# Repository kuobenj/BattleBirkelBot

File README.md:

# BirkelBot Battlebot Repo
This repository is for the code and other files related to Team Unobtanium's Battlebot for the Combotics competition held annually at the University of Illinois at Urbana Champaign.

Team Unobtanium is:
* Matt Birkel - Team Captain, Mechanical Design, Software
* Benjamin Kuo - Electrical Design, Software

### Folder Structure
* Robot - This is robot side code. For now this should largely be arduino code for the arduino on board the robot.
* DriverStation - This is the operator side code. This is the code that runs on a driverstation computer.
* Arduino_Calibration_Stuff - This is a folder for a tool to use the arduino to calibrate ESC's
* PCB_files is a directory that holds the EAGLE files for the custom "motherboard" for the robot. This directory also features a reworked design of a PCB for hall effect sensors to sensor 35mm outrunner brushless motors.

### Dependencies
The Robot code is written for an Arduino Pro Mini. As such the Arduino IDE is required to compile and upload the Arduino-side code. The Arduino IDE offers a variety of Libraries for use. This project utilizes

* Encoder by Paul Stoffregen (version 1.4.1)
* PID by Brett Beauregard (version 1.2.0)

To install these libraries

- Go to 'Sketch' -> 'Include Library' -> 'Manage Libraries...'
- Search '<package-name>'
- Install '<package-name>'

The DriverStation code is a pythons script. Below are a potentially non-exhaustive list of the required dependencies.

* pygame - For grabbing joystick values
* serial - For writing to the serial out for the Xbee communication

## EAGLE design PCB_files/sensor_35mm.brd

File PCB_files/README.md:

The sensor_35mm files are all inspired by Equals Zero Designs

"Mount CAD" directory is for the mount to the motor for the sensors

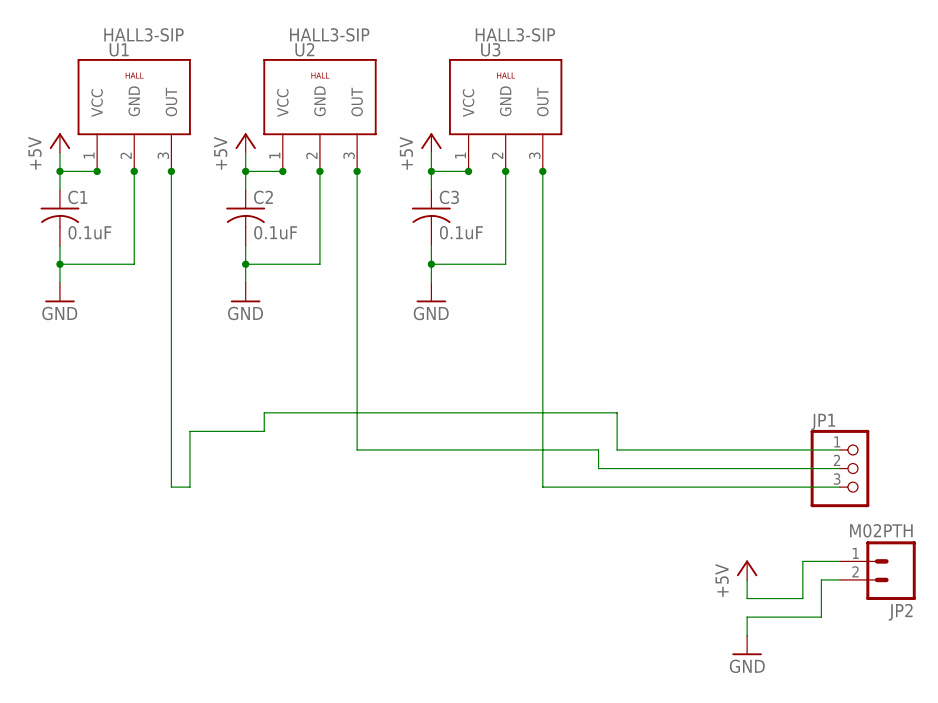
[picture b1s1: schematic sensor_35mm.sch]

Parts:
C1, C2, C3: 0.1uF; C0603
JP1: PINHD-1X3CB; 1X03-CLEANBIG
JP2: M02PTH; 1X02
U1, U2, U3: HALL3-SIP; 3PINS1,27

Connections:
+5V: C1.1, C2.1, C3.1, JP2.1, U1.1 (VCC), U2.1 (VCC), U3.1 (VCC)
GND: C1.2, C2.2, C3.2, JP2.2, U1.2 (GND), U2.2 (GND), U3.2 (GND)
unnamed: JP1.1, U1.3 (OUT)
unnamed: JP1.3, U3.3 (OUT)
unnamed: JP1.2, U2.3 (OUT)

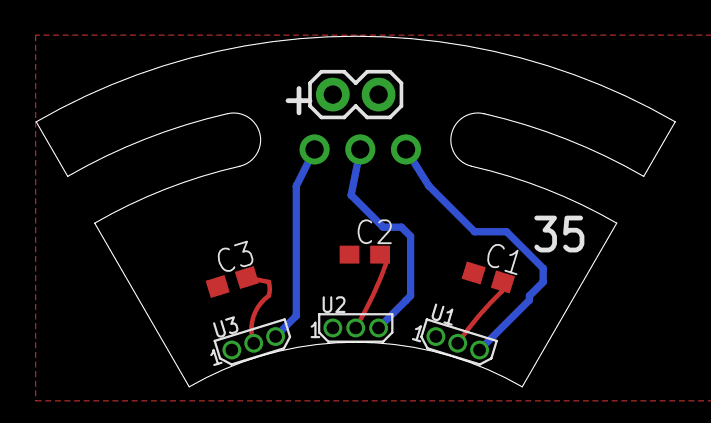
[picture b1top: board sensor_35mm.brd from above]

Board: 2 copper layers, 35.5 x 19.5 mm, 8 parts (0 on the bottom side), 5 nets.

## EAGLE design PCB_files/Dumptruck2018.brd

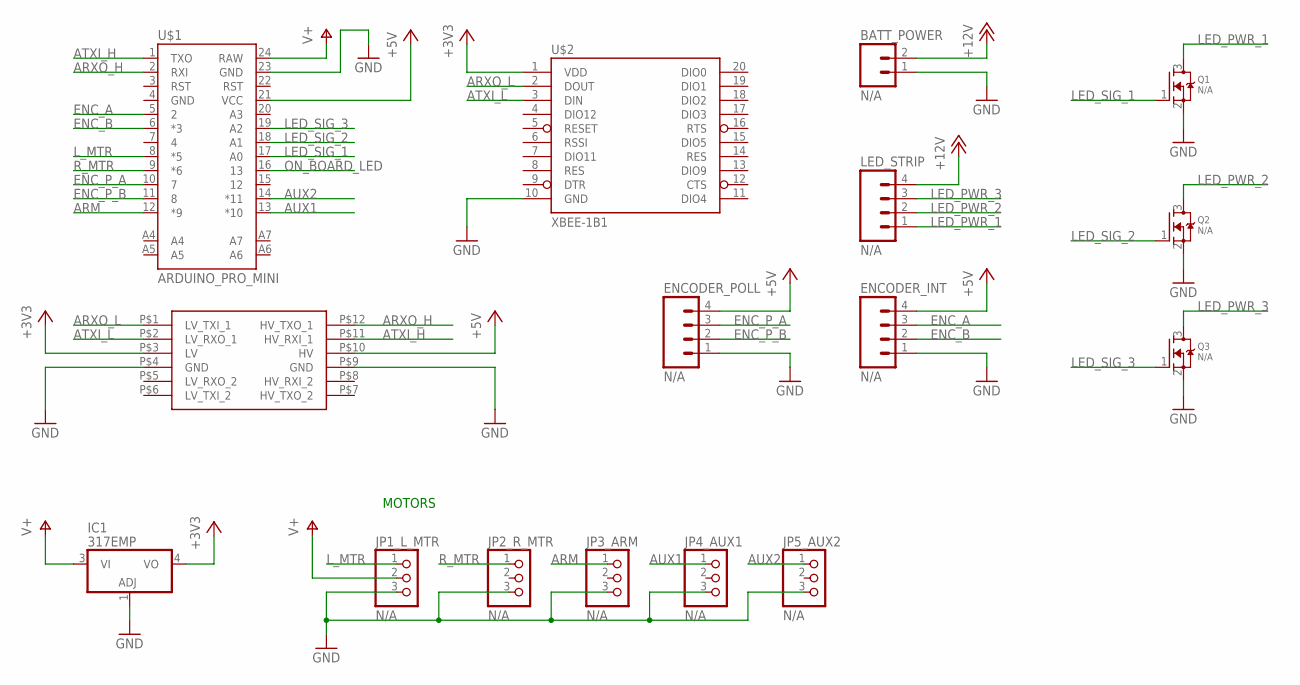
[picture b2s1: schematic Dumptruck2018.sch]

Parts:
BATT_POWER: N/A; 1X02
ENCODER_INT: N/A; 1X04_LOCK
ENCODER_POLL: N/A; 1X04_LOCK
IC1: 317EMP; SOT223
JP1_L_MTR, JP2_R_MTR, JP3_ARM, JP4_AUX1, JP5_AUX2: N/A; 1X03
LED_STRIP: N/A; 1X04_LOCK
Q1, Q2, Q3: N/A; SOT23
U$1: ARDUINO_PRO_MINI
U$2: XBEE-1B1; XBEE-1
U$3: LOGIC_LEVEL_CONVERTER

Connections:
+3V3: IC1.4 (VO), U$2.1 (VDD), U$3.P$3 (LV)
+5V: ENCODER_INT.4, ENCODER_POLL.4, U$1.21 (VCC), U$3.P$10 (HV)
+12V: BATT_POWER.2, LED_STRIP.4
ARM: JP3_ARM.1, U$1.12 (*9)
ARXO_H: U$1.2 (RXI), U$3.P$12 (HV_TXO_1)
ARXO_L: U$2.2 (DOUT), U$3.P$1 (LV_TXI_1)
ATXI_H: U$1.1 (TXO), U$3.P$11 (HV_RXI_1)
ATXI_L: U$2.3 (DIN), U$3.P$2 (LV_RXO_1)
AUX1: JP4_AUX1.1, U$1.13 (*10)
AUX2: JP5_AUX2.1, U$1.14 (*11)
ENC_A: ENCODER_INT.3, U$1.5 (2)
ENC_B: ENCODER_INT.2, U$1.6 (*3)
ENC_P_A: ENCODER_POLL.3, U$1.10 (7)
ENC_P_B: ENCODER_POLL.2, U$1.11 (8)
GND: BATT_POWER.1, ENCODER_INT.1, ENCODER_POLL.1, IC1.1 (ADJ), JP1_L_MTR.3, JP2_R_MTR.3, JP3_ARM.3, JP4_AUX1.3, JP5_AUX2.3, Q1.2 (S), Q2.2 (S), Q3.2 (S), U$1.23 (GND), U$2.10 (GND), U$3.P$4 (GND), U$3.P$9 (GND)
LED_PWR_1: LED_STRIP.1, Q1.3 (D)
LED_PWR_2: LED_STRIP.2, Q2.3 (D)
LED_PWR_3: LED_STRIP.3, Q3.3 (D)
LED_SIG_1: Q1.1 (G), U$1.17 (A0)
LED_SIG_2: Q2.1 (G), U$1.18 (A1)
LED_SIG_3: Q3.1 (G), U$1.19 (A2)
L_MTR: JP1_L_MTR.1, U$1.8 (*5)
ON_BOARD_LED: U$1.16 (13)
R_MTR: JP2_R_MTR.1, U$1.9 (*6)
V+: IC1.3 (VI), JP1_L_MTR.2, U$1.24 (RAW)

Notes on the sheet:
MOTORS

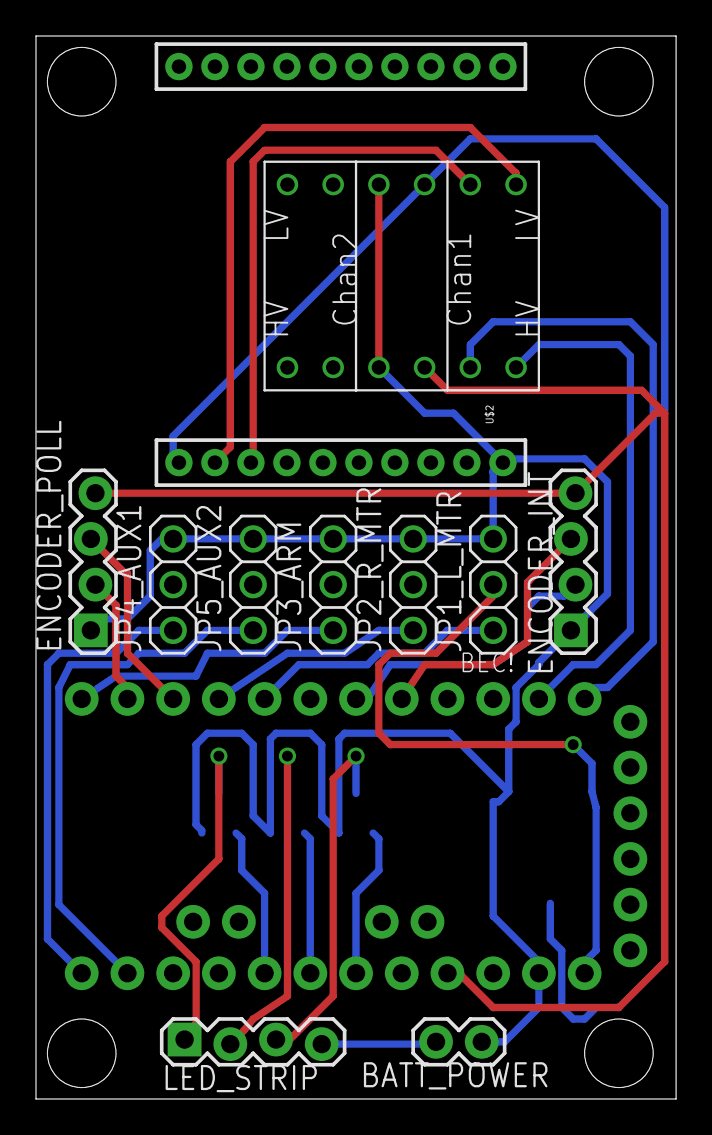
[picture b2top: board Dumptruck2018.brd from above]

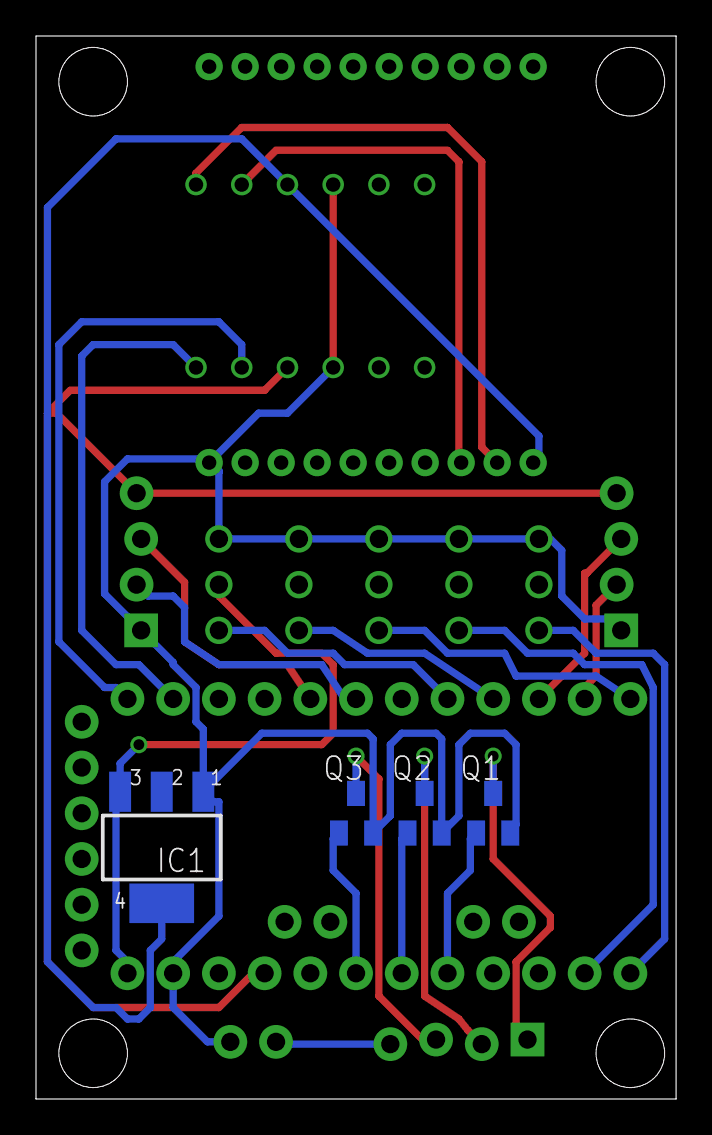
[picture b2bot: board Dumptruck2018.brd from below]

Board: 2 copper layers, 35.6 x 59.1 mm, 16 parts (4 on the bottom side), 24 nets.

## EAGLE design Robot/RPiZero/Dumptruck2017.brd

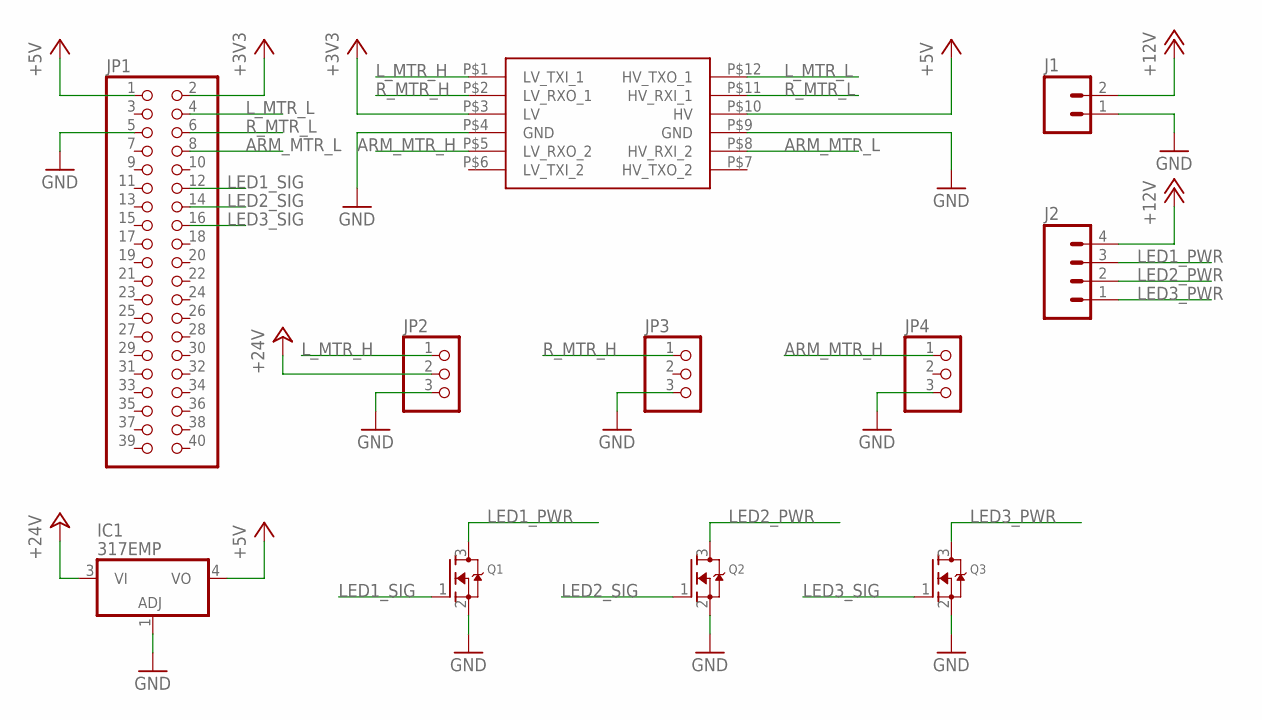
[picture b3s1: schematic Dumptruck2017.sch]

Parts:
IC1: 317EMP; SOT223
J1: M02LOCK; 1X02_LOCK
J2: M04LOCK; 1X04_LOCK
JP1: PINHD-2X20; 2X20
JP2, JP3, JP4: PINHD-1X3; 1X03
Q1, Q2, Q3: MOSFET-NREFLOW; SOT23
U$1: LOGIC_LEVEL_CONVERTER

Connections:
+3V3: JP1.2, U$1.P$3 (LV)
+5V: IC1.4 (VO), JP1.1, U$1.P$10 (HV)
+12V: J1.2, J2.4
+24V: IC1.3 (VI), JP2.2
ARM_MTR_H: JP4.1, U$1.P$5 (LV_RXO_2)
ARM_MTR_L: JP1.8, U$1.P$8 (HV_RXI_2)
GND: IC1.1 (ADJ), J1.1, JP1.5, JP2.3, JP3.3, JP4.3, Q1.2 (S), Q2.2 (S), Q3.2 (S), U$1.P$4 (GND), U$1.P$9 (GND)
LED1_PWR: J2.3, Q1.3 (D)
LED1_SIG: JP1.12, Q1.1 (G)
LED2_PWR: J2.2, Q2.3 (D)
LED2_SIG: JP1.14, Q2.1 (G)
LED3_PWR: J2.1, Q3.3 (D)
LED3_SIG: JP1.16, Q3.1 (G)
L_MTR_H: JP2.1, U$1.P$1 (LV_TXI_1)
L_MTR_L: JP1.4, U$1.P$12 (HV_TXO_1)
R_MTR_H: JP3.1, U$1.P$2 (LV_RXO_1)
R_MTR_L: JP1.6, U$1.P$11 (HV_RXI_1)

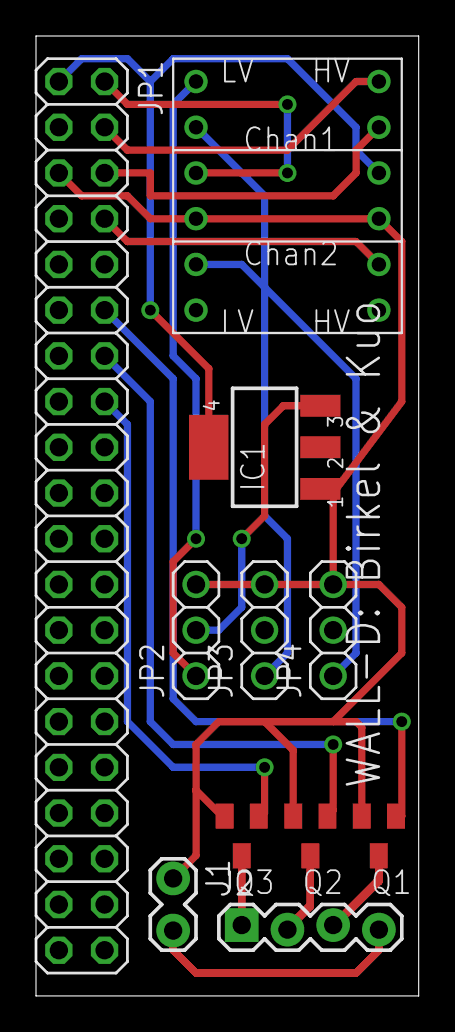
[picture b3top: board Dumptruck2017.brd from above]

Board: 2 copper layers, 21.3 x 53.3 mm, 11 parts (0 on the bottom side), 17 nets.

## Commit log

2016-02-23 Added initial driver station scripts, based on Moser's code from 2015
2016-03-14 Final working competition code
2016-12-18 removed everything we don't need I think, changed H-drive to tank drive, added RPi GPIO stuff, technically everything should work, but I'd need to test
2016-12-29 eagle cad pcb stuff added
2017-01-01 made some changes to the arm code
2017-01-01 made final changes to shrink board a bit and ordered this version
2017-02-24 Moved/renamed things around a bit
2017-02-24 Copied the arcadeDrive code from the RPiZero python into the DriverStation python. Updated the arm command to use the same exponential control as the drive commands. Added comments.
2017-02-24 Removed the 'mid' motor code from the ArduinoProMini. Still need to add changing LEDs based on arm raise/lower.
2017-02-28 my RPi GPIO stuff
2017-02-28 changed pins to new pin outs, also added LED control code
2017-03-01 everything works!
2017-12-11 adding calibration file, not sure what that's for
2017-12-12 old inventor file for some rev of the pcb, committing but will delete later
2017-12-12 removing files not relevant to this year
2017-12-12 remapped the pins, added some comments, added encoder code
2017-12-26 a couple of returns added, no major changes
2017-12-28 wrote some preliminary code for PID, definitely will need more work
2018-02-07 adding PCB_files
2018-02-12 Confirm and rename LED strip pins
2018-02-12 Bailout if any received value is invalid
2018-02-19 Added Auto/Manual mode for arm. Auto has 3 positions (lowest, low, high), depending on number of buttons pressed. Manual allows to control speed using analog triggers. There is also a function to res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
2018-02-19 Read extra flags command in Arduino code, and hold manual/auto and zero states.
2018-02-20 tabs to spaces
2018-02-25 Simulate joystick input from keyboard
2018-02-26 Refactor code
2018-02-26 Add arm cmds for client to set Kp, Ki, Kd PID values
2018-02-28 Add remote setup cmd for PID gains
2018-02-28 Add arm angle mode
2018-02-28 Comment out all local test code and debug output
2018-03-01 Quick cleanup of Arduino_Calibration_Stuff
2018-03-03 Changes for auto/manual arm mode and reserved values
2018-03-05 Added manual bumper control, sending of PID gains setup message, bugfixes, and LED colors on Arduino
2018-03-05 Removed some print lines/unused code
2018-03-06 Wait for Serial.available in processSetup
2018-03-08 Tuned PID gains, send mode on DS bootup, changed control scheme
2018-03-08 Added default PID gains from tuning, altered comms protocol to re-sync when off sync
2018-03-08 Added joystick watchdog for failsafe
2018-03-15 Flipped motors after recalibrating ESCs
2019-01-10 Adding Sensor Board Files and Updating README
    This year an additional PCB was needed for use for
    brushless motors. A sensor board was not made for
    35mm motors and this commit contains those files.

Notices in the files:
parts and their libraries:
SparkFun-Boards: Licensing: Creative Commons ShareAlike 4.0 International - https://creativecommons.org/licenses/by-sa/4.0
